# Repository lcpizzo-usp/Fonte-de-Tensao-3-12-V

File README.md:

# Fonte de Tensão Ajustável
Fonte de tensão ajustável desenvolvida para a disciplina [SSC0180 - Eletrônica para Computação](https://uspdigital.usp.br/jupiterweb/obterDisciplina?sgldis=SSC0180&verdis=2) do Curso de Ciência da Computação da USP - São Carlos

## Lista de Componentes
Componente           | Especificações            | Quantidade          | Valor (un.)        
:--------------------|:--------------------------|:--------------------|:-------------
[Resistor](https://www.baudaeletronica.com.br/resistor-2k2-5-1-4w.htmll)      | 2k2Ω | 1 |   R$0,08
[Resistor](https://www.baudaeletronica.com.br/resistor-5k1-5-1-4w.html)      | 5k1Ω | 1 |   R$0,08
[Potenciômetro](https://www.baudaeletronica.com.br/potenciometro-linear-de-10k-10000.html) | 10k | 1 | R$1,54
[Capacitor](https://www.baudaeletronica.com.br/capacitor-eletrolitico-470uf-25v.html)     | 25V / 470μF | 1 |   R$0,33
[Diodo](https://www.baudaeletronica.com.br/diodo-zener-zmm-22v-0-5w.html)         | 22V / 0,5W | 4 |   R$0,15
[Diodo Zener](https://www.baudaeletronica.com.br/diodo-zener-zmm-13v-0-5w.html)  | 13V / 0,5W | 1 | R$0,09
[Transistor](https://www.baudaeletronica.com.br/transistor-npn-2n3904.html)    | 2N3904 | 1 |   R$0,18 
[Transformador](https://www.baudaeletronica.com.br/transformador-trafo-1a-24v.html) | 24V / 1mA | 1 |   R$36,00

Total: R$39,00

### Explicação dos Componentes
1. Transformador: O transformador é usado para reduzir a tensão da tomada de 127V, no caso, para 24V. Foi usado um transformador com razão 24/127;
2. Diodo: Os diodos são usados em configuração de ponte retificadora de corrente alternada, invertendo uma das fases da corrente alternada;
3. Capacitor: O capacitor é usado para fornecer energia ao circuito em momentos em que a corrente tende a zero;
4. Diodo Zener: O diodo zener é usado para regular a tensão que passa pela saída do circuito;
5. Pontenciômetro: O potenciômetro é usado para ajustar a tensão de saída do circuito;
6. Resistor: o resistor de 2k2 é usado para reduzir a corrente que passa pelo diodo zener, e para impedir um curto circuito se a tensão for menor que 13V  e o outro é usado para oferecer um "valor mínimo" de 3V no circuito, sem ele, ao reduzir a resistência no potenciômetro a tensão na saída seria zero;
7. Transistor: é um multiplicador de corrente no circuito.
#### Vídeo
https://youtu.be/aY4b_8o9HOc

## Imagens
### Simulação do Circuito 

Simulação feita pelo falstad: http://tinyurl.com/y7m4rmxe
### Diagrama do Circuito (Esquemático)

### PCB (Printed Circuit Board) 

## Participantes

* **Leonardo Chagas Pizzo** - [lcpizzo-usp](https://github.com/lcpizzo-usp)

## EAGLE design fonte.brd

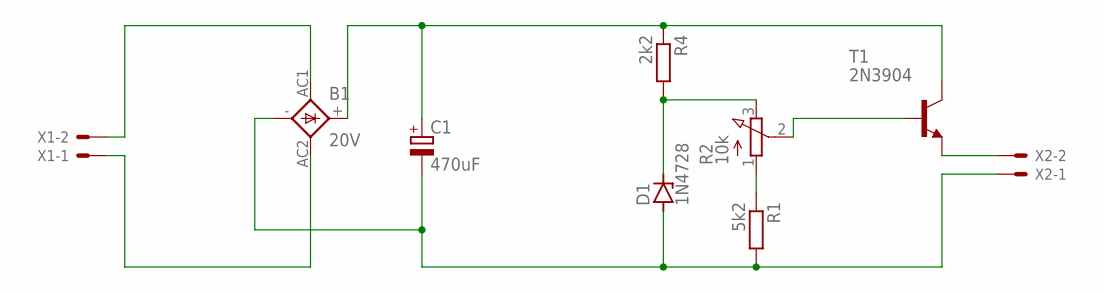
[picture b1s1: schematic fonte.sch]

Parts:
B1: 20V; 1KAB
C1: 470uF; E2,5-6E
D1: 1N4728; DO41Z10
R1: 5k2; 0207/10
R2: 10k; 3RP/1610N
R4: 2k2; 0207/10
T1: 2N3904; TO92
X1, X2: 22-23-2021

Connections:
unnamed: B1.AC1, X1.2
unnamed: B1.-, C1.-, D1.A, R1.2, X2.1
unnamed: R1.1, R2.1 (A)
unnamed: D1.C, R2.3 (E), R4.2
unnamed: R2.2 (S), T1.2 (B)
unnamed: B1.+, C1.+, R4.1, T1.1 (C)
unnamed: B1.AC2, X1.1
unnamed: T1.3 (E), X2.2

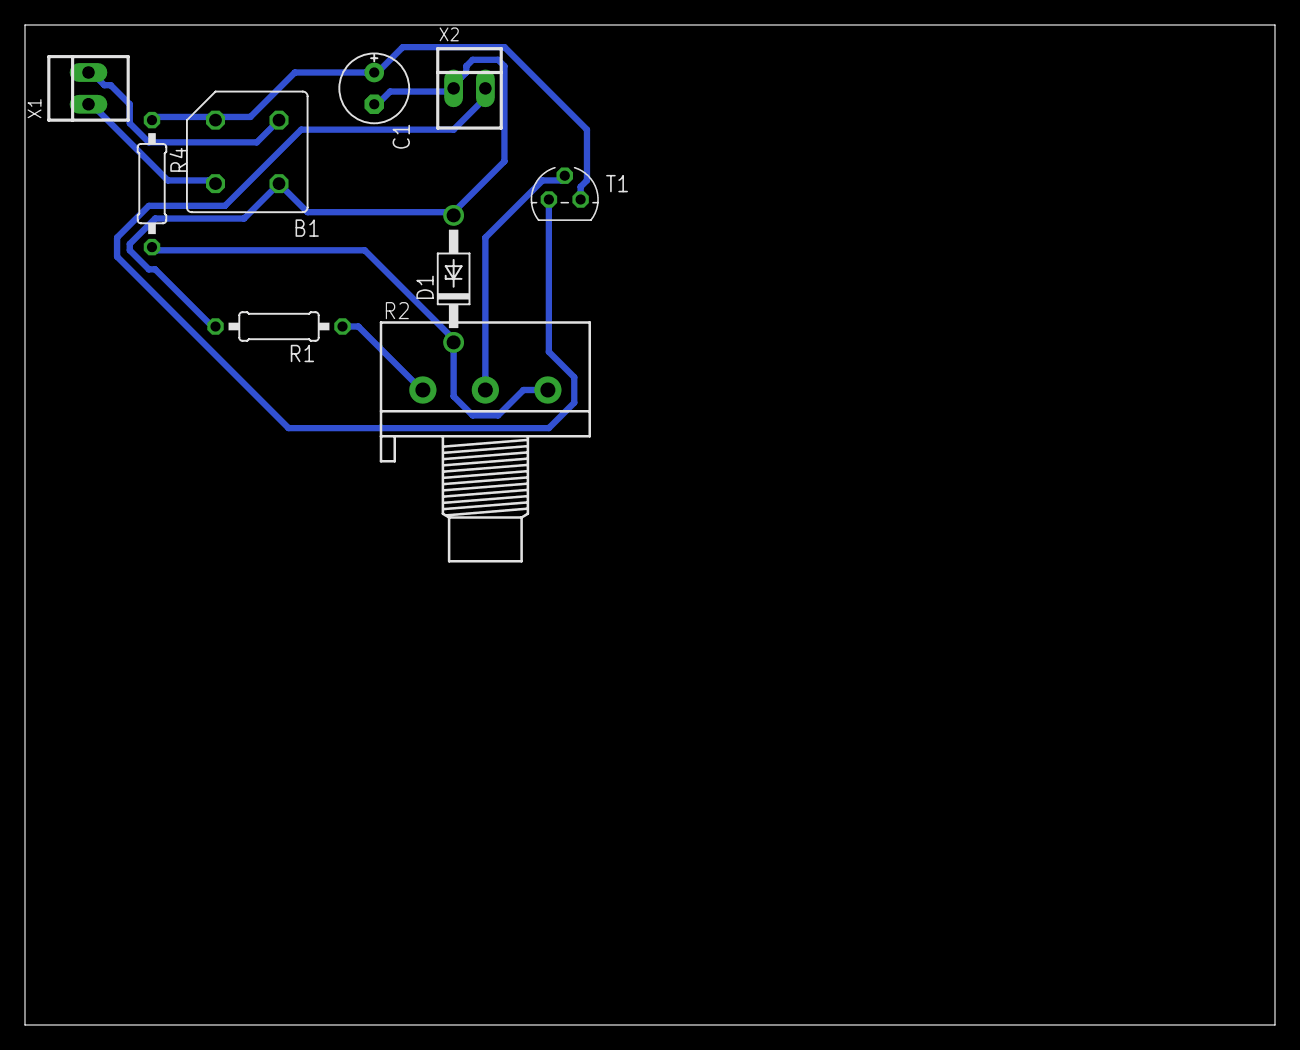
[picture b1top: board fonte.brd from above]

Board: 2 copper layers, 100.0 x 80.0 mm, 9 parts (0 on the bottom side), 8 nets.
